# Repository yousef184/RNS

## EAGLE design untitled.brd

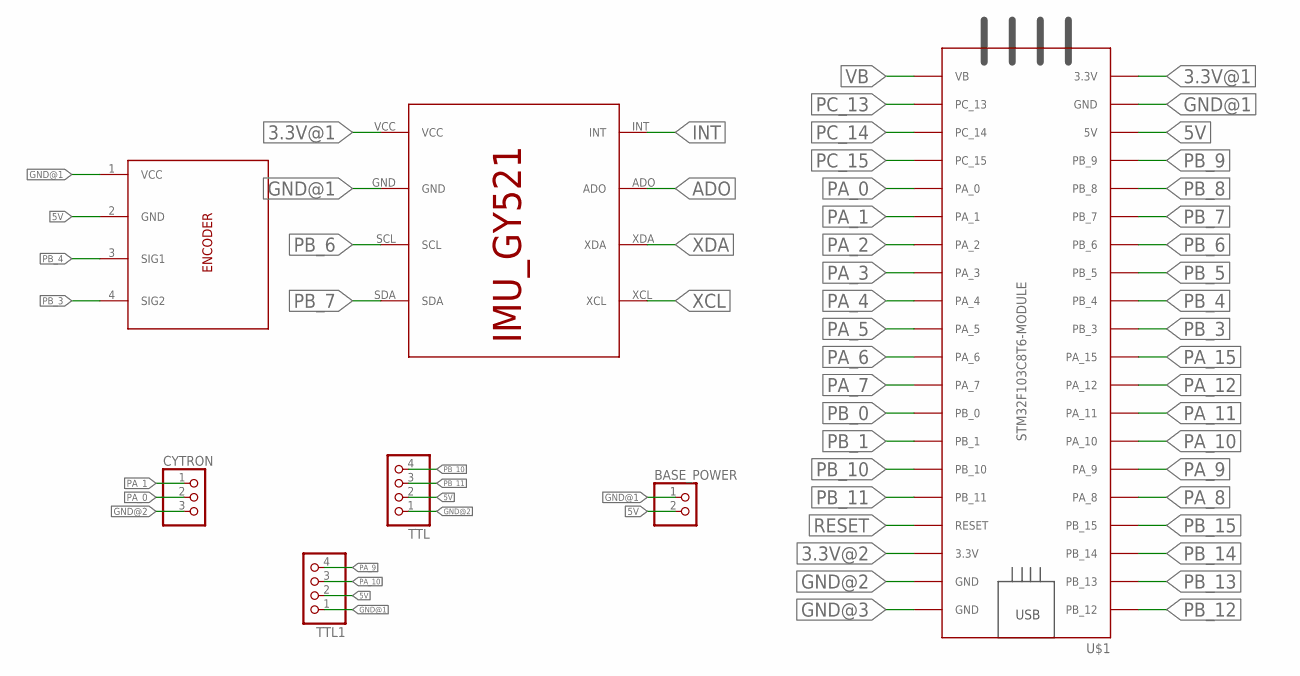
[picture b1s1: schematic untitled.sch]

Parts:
BASE_POWER: PINHD-2_DATA; 1X02_DATA
CYTRON: PINHD-3_DATA; 1X03_DATA
TTL, TTL1: PINHD-4_DATA; 1X04_DATA
U$1: STM32F103C8T6-MODULE
U$2: IMU_ROBOCON_GY521; IMU_GY521
U$3: ENCODER; 1X04_DATA

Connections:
3.3V@1: U$1.3.3V_1 (3.3V), U$2.VCC
3.3V@2: U$1.3.3V_2 (3.3V)
5V: BASE_POWER.2, TTL.2, TTL1.2, U$1.5V, U$3.2 (GND)
ADO: U$2.ADO
GND@1: BASE_POWER.1, TTL1.1, U$1.GND_1 (GND), U$2.GND, U$3.1 (VCC)
GND@2: CYTRON.3, TTL.1, U$1.GND_2 (GND)
GND@3: U$1.GND_3 (GND)
INT: U$2.INT
PA_0: CYTRON.2, U$1.PA_0
PA_1: CYTRON.1, U$1.PA_1
PA_2: U$1.PA_2
PA_3: U$1.PA_3
PA_4: U$1.PA_4
PA_5: U$1.PA_5
PA_6: U$1.PA_6
PA_7: U$1.PA_7
PA_8: U$1.PA_8
PA_9: TTL1.4, U$1.PA_9
PA_10: TTL1.3, U$1.PA_10
PA_11: U$1.PA_11
PA_12: U$1.PA_12
PA_15: U$1.PA_15
PB_0: U$1.PB_0
PB_1: U$1.PB_1
PB_3: U$1.PB_3, U$3.4 (SIG2)
PB_4: U$1.PB_4, U$3.3 (SIG1)
PB_5: U$1.PB_5
PB_6: U$1.PB_6, U$2.SCL
PB_7: U$1.PB_7, U$2.SDA
PB_8: U$1.PB_8
PB_9: U$1.PB_9
PB_10: TTL.4, U$1.PB_10
PB_11: TTL.3, U$1.PB_11
PB_12: U$1.PB_12
PB_13: U$1.PB_13
PB_14: U$1.PB_14
PB_15: U$1.PB_15
PC_13: U$1.PC_13
PC_14: U$1.PC_14
PC_15: U$1.PC_15
RESET: U$1.RESET
VB: U$1.VB
XCL: U$2.XCL
XDA: U$2.XDA

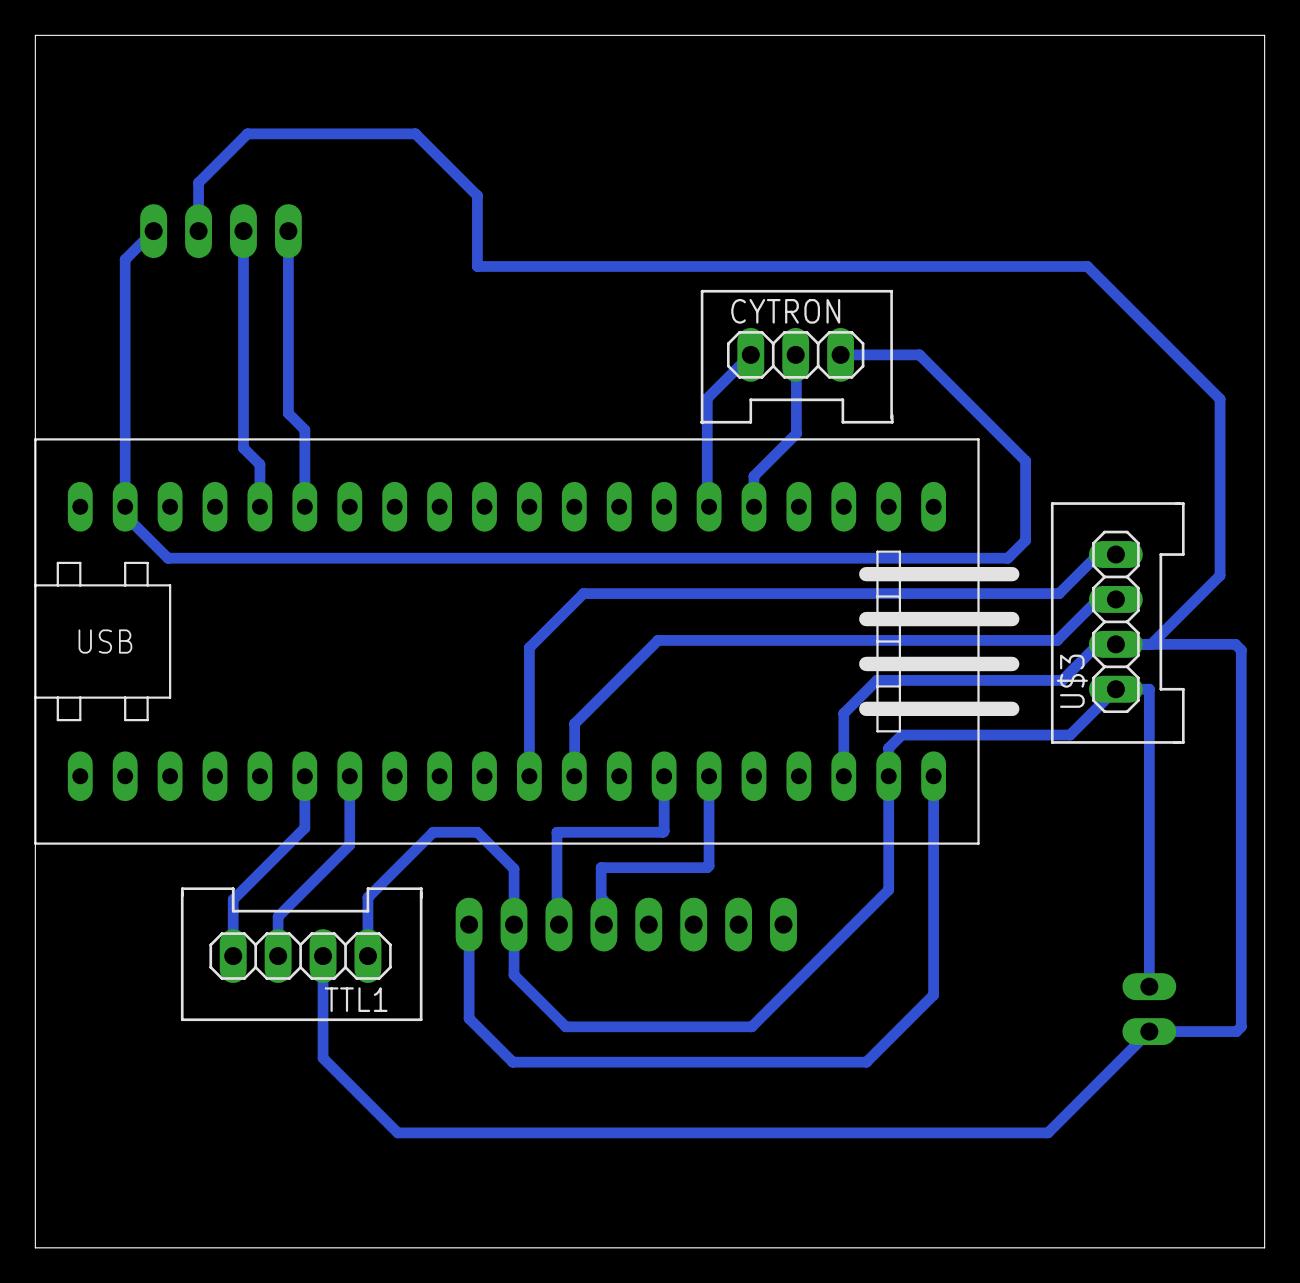
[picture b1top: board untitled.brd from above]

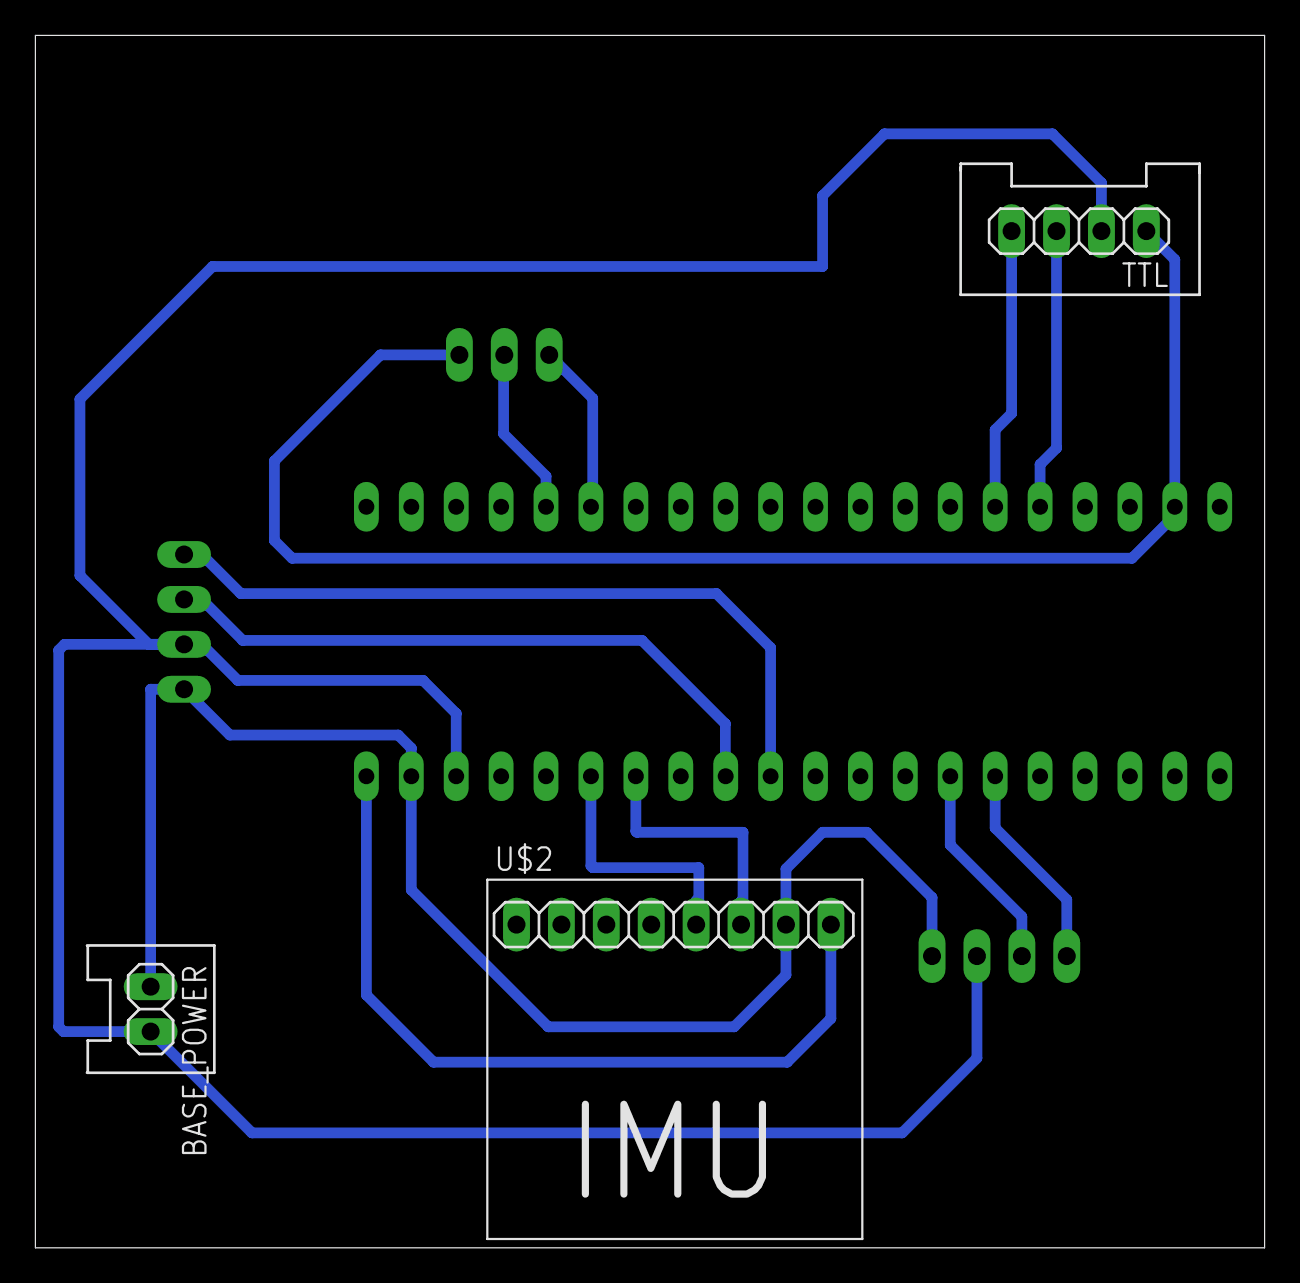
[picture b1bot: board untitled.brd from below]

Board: 2 copper layers, 69.5 x 68.6 mm, 7 parts (3 on the bottom side), 14 nets.
